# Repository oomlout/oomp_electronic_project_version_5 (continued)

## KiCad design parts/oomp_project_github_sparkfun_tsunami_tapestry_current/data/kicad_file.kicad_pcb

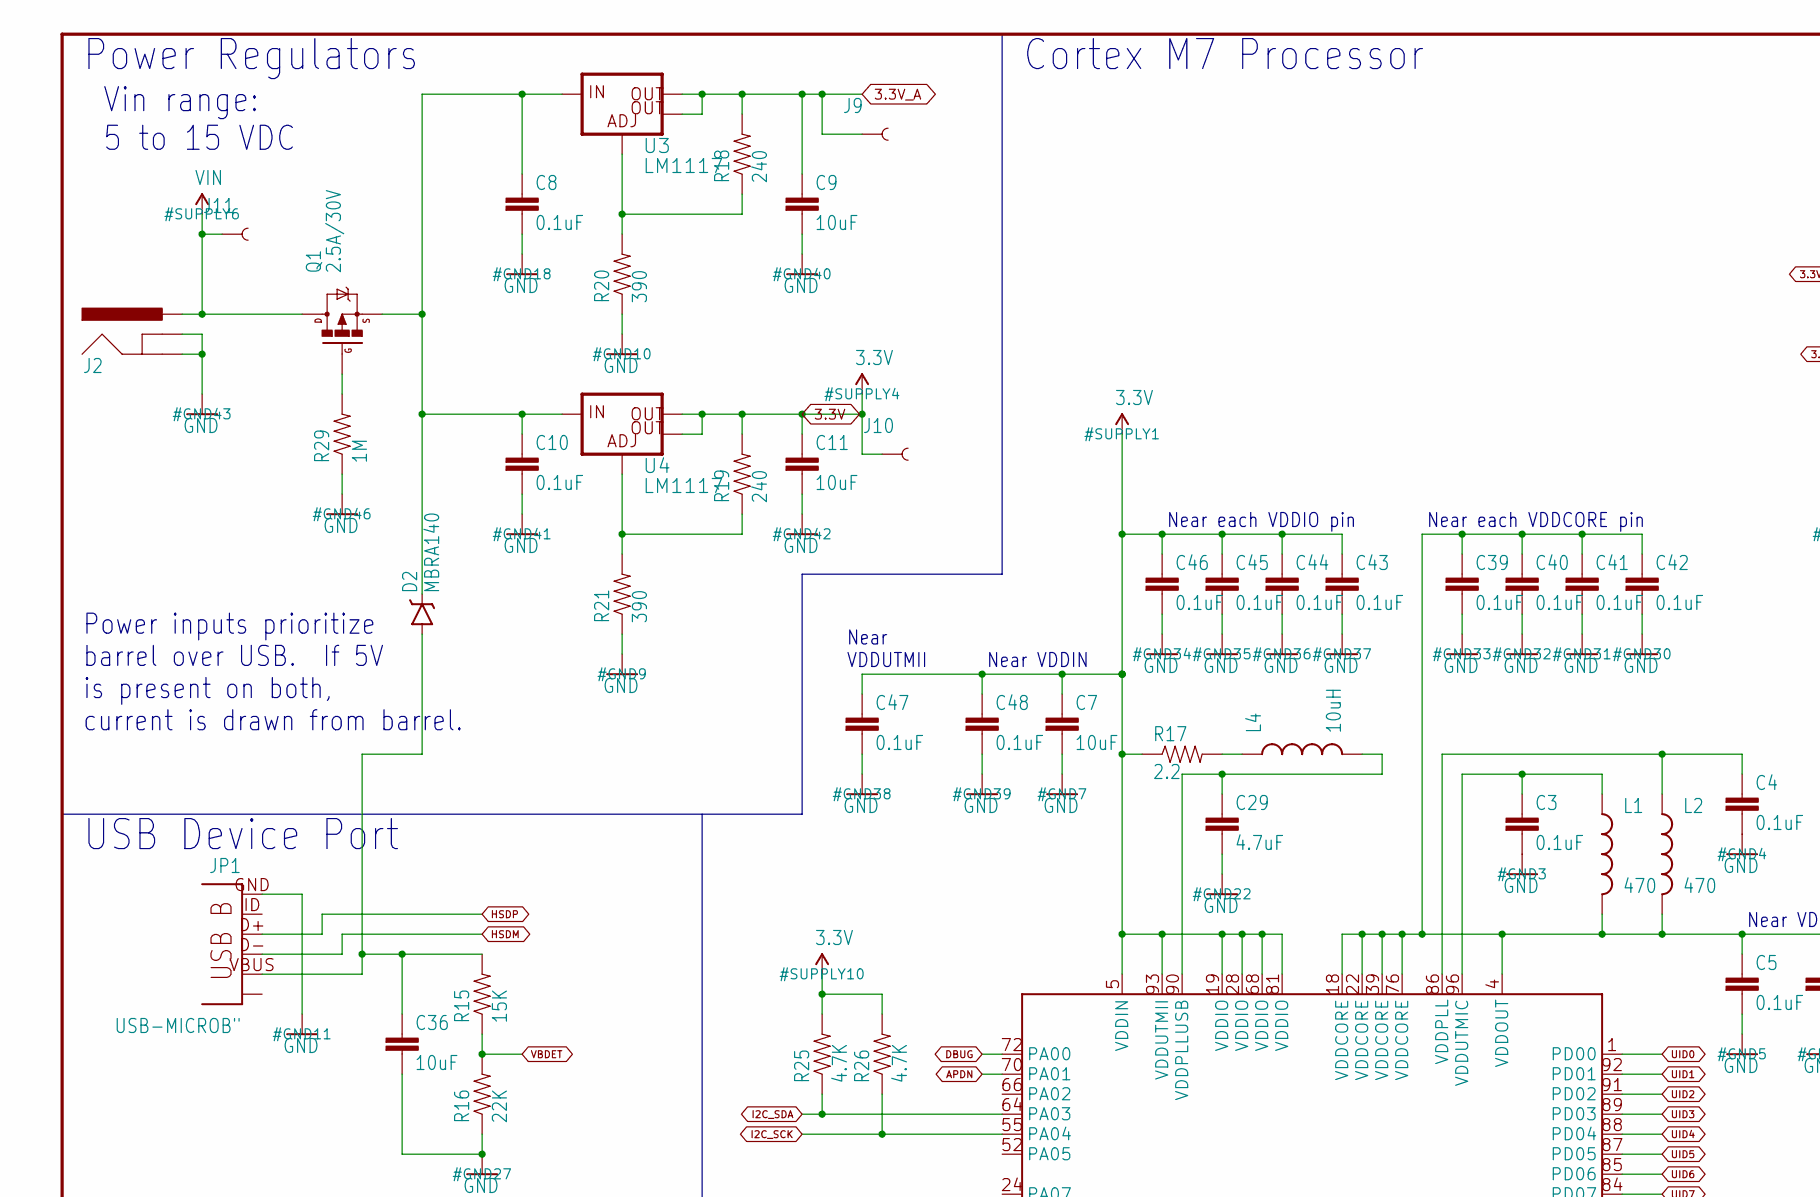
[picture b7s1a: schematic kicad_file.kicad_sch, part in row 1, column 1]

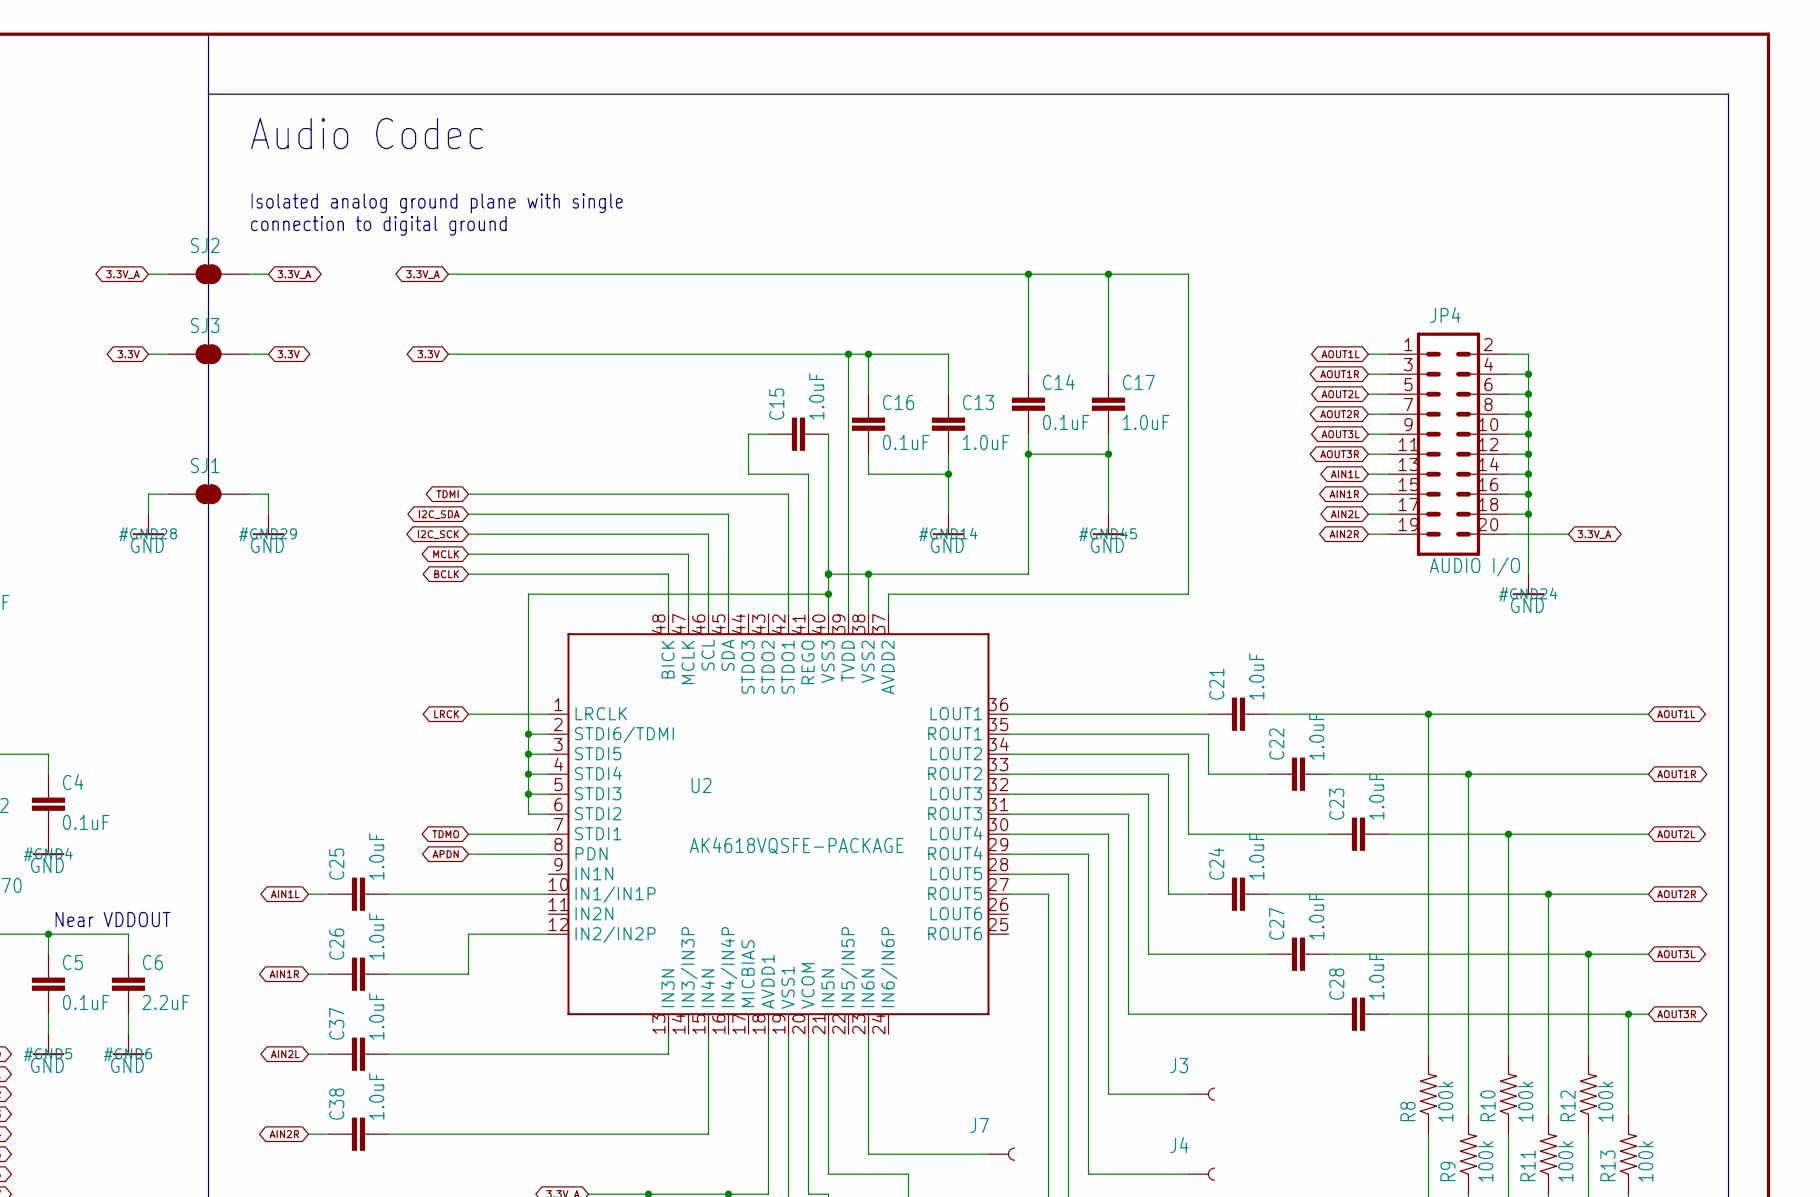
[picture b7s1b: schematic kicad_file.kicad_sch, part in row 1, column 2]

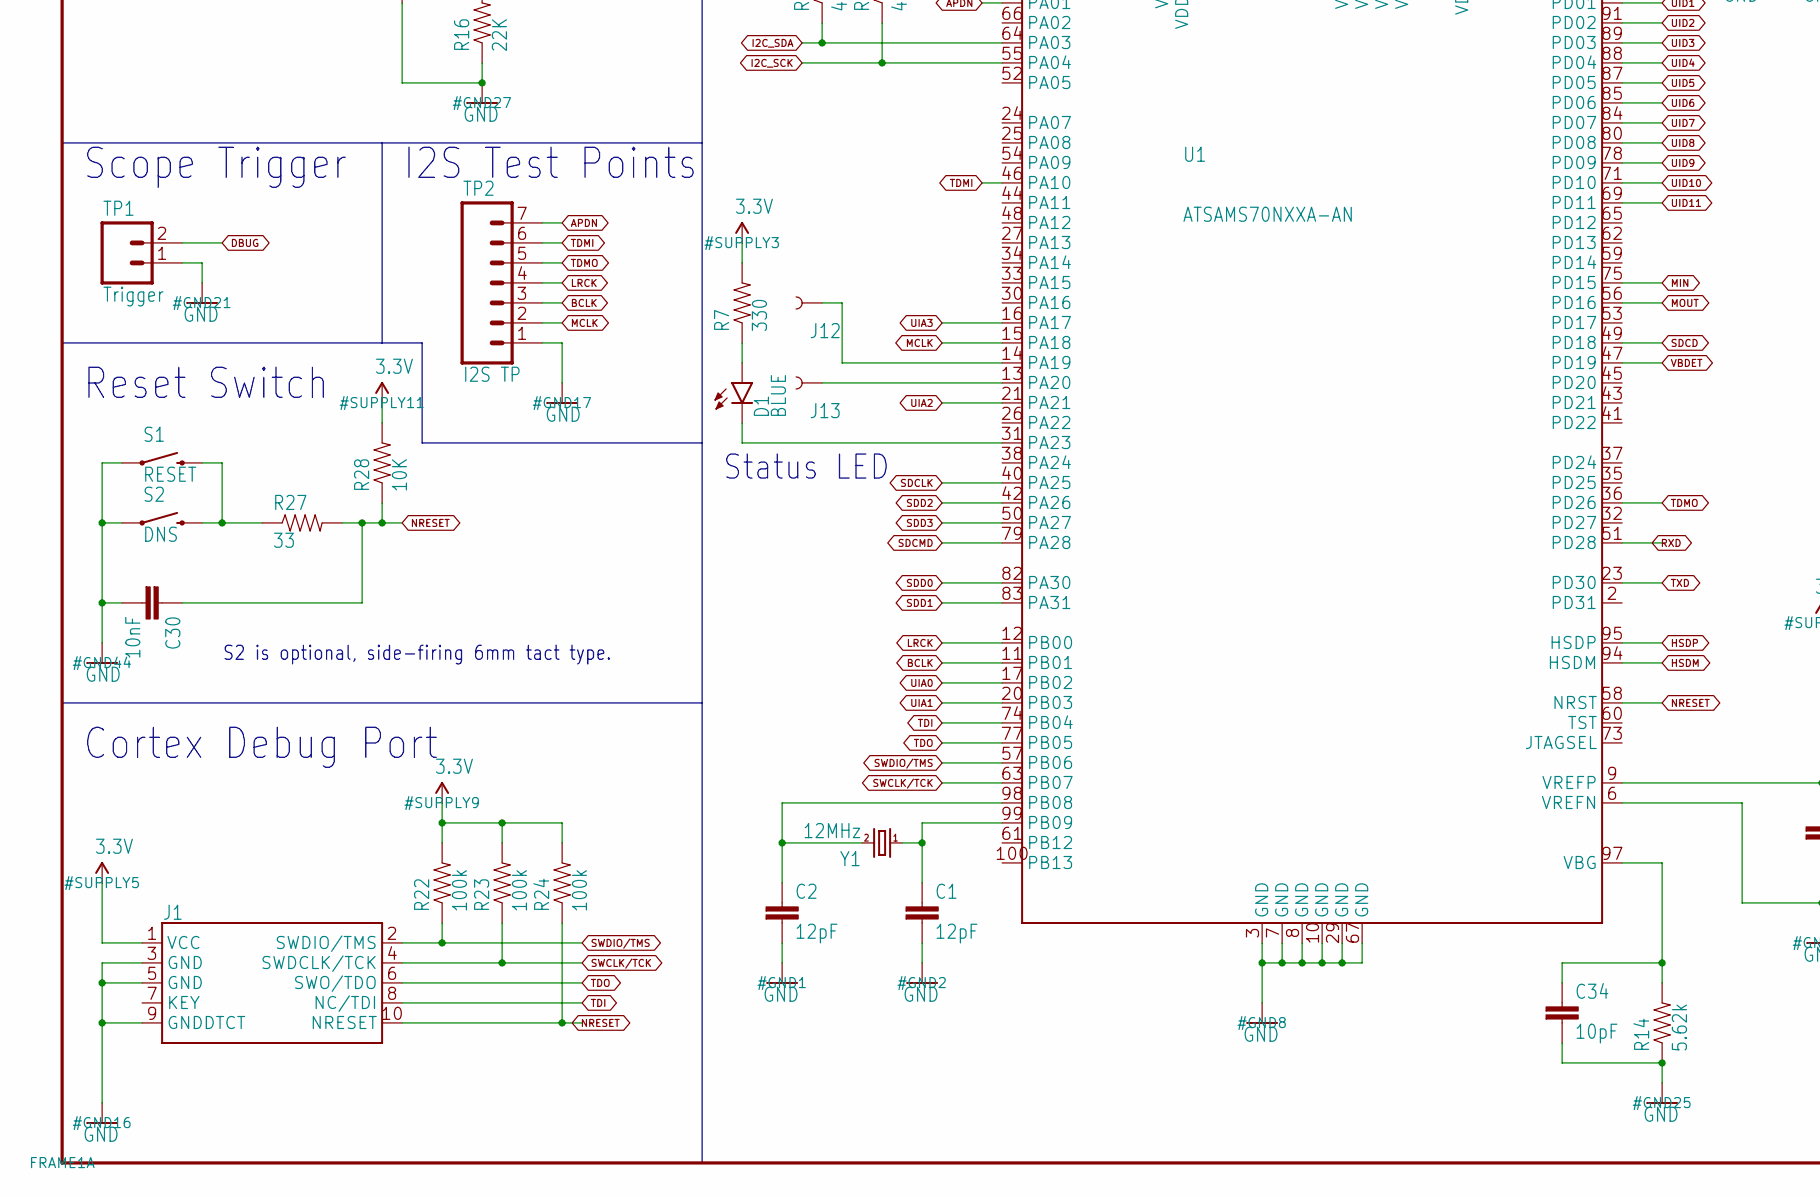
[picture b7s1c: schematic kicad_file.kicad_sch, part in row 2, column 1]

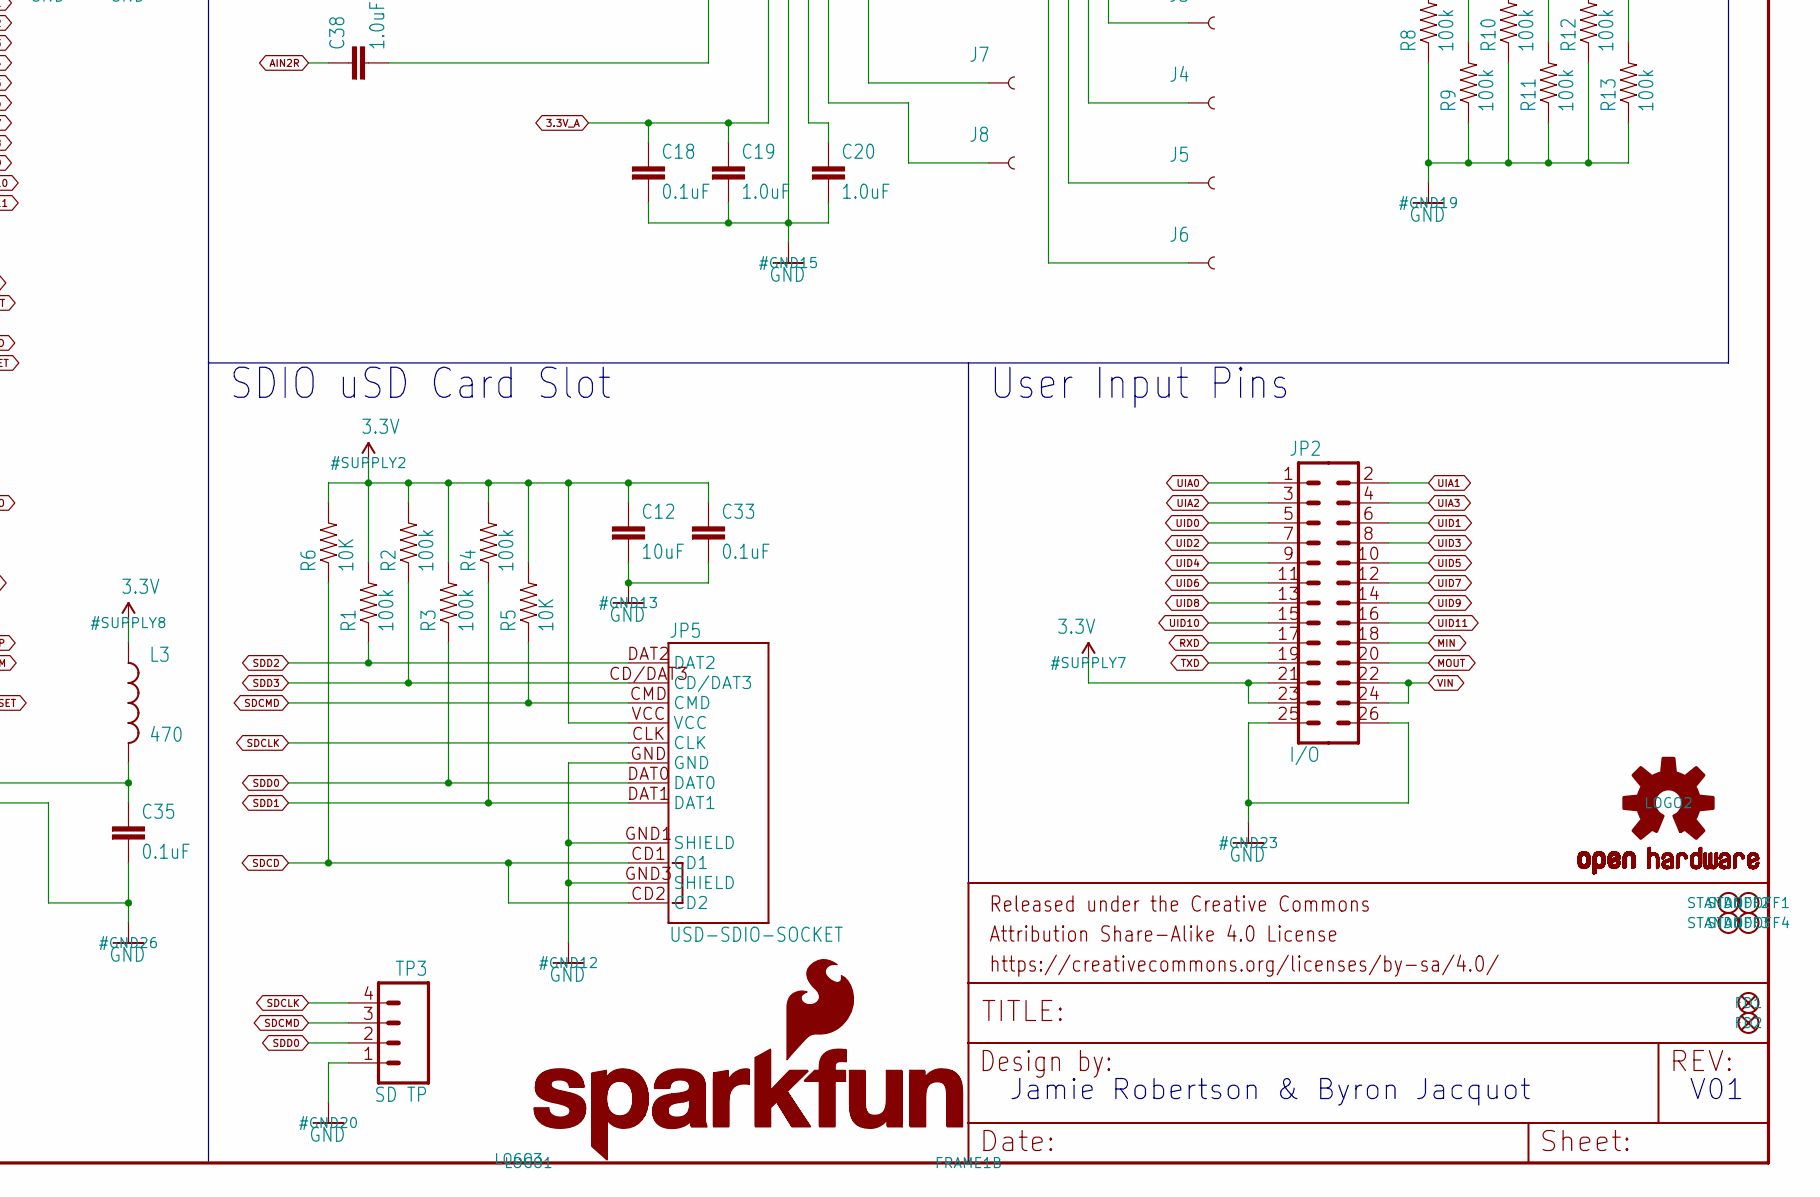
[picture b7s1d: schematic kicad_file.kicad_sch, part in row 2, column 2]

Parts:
C1, C2: 12pF; 0603-CAP
C3, C4, C5, C8, C10, C14, C16, C18, C33, C35, C39, C40, C41, C42, C43, C44, C45, C46, C47, C48: 0.1uF; 0603-CAP
C6: 2.2uF; 0603-CAP
C7, C9, C11, C12, C36: 10uF; 0603-CAP
C13, C15, C17, C19, C20, C21, C22, C23, C24, C25, C26, C27, C28, C37, C38: 1.0uF; 0603-CAP
C29: 4.7uF; 0603-CAP
C30: 10nF; 0603-CAP
C34: 10pF; 0603-CAP
D1: BLUE; LED-0603
D2: MBRA140; SMA-DIODE
FD1, FD2: FIDUCIALUFIDUCIAL; MICRO-FIDUCIAL
FRAME1: FRAME-LEDGER; CREATIVE_COMMONS
J1: CORTEX_DEBUGPTH; 2X5-PTH-1.27MM
J2: POWER_JACK DNS; POWER_JACK_PTH_LOCK
J3: AOUT4L; TP_15TH
J4: AOUT4R; TP_15TH
J5: AOUT5L; TP_15TH
J6: AOUT5R; TP_15TH
J7: AIN3R; TP_15TH
J8: AIN3L; TP_15TH
J9: 3.3VA; TP_15TH
J10: 3.3V; TP_15TH
J11: VIN; TP_15TH
J12: A4; TP_15TH
J13: A5; TP_15TH
JP1: USB-MICROB"; USB-B-MICRO-SMD_V03
JP2: I/O; 2X13
JP4: AUDIO I/O; 2X10
JP5: USD-SDIO-SOCKET; MICRO-SD-SOCKET-SDIO
L1, L2, L3: 470; 0603
L4: 10uH; 0805
LOGO1: SFE_LOGO_NAME_FLAME.2_INCH; SFE_LOGO_NAME_FLAME_.2
LOGO2: OSHW-LOGOM; OSHW-LOGO-M
LOGO3: SFE_LOGO_NAME.2_INCH; SFE_LOGO_NAME_.2
Q1: 2.5A/30V; SOT23-3
R1, R2, R3, R4, R8, R9, R10, R11, R12, R13, R22, R23, R24: 100k; 0603-RES
R5, R6, R28: 10K; 0603-RES
R7: 330; 0603-RES
R14: 5.62k; 0603-RES
R15: 15K; 0603-RES
R16: 22K; 0603-RES
R17: 2.2; 0603-RES
R18, R19: 240; 0603-RES
R20, R21: 390; 0603-RES
R25, R26: 4.7K; 0603-RES
R27: 33; 0603-RES
R29: 1M; 0603-RES
S1: RESET; TACTILE-SWITCH-SMD
S2: DNS; TACTILE-PTH-SIDEEZ
SJ1, SJ2, SJ3: JUMPER-PAD-2-NC_BY_TRACE; PAD-JUMPER-2-NC_BY_TRACE_YES_SILK
STANDOFF1, STANDOFF2, STANDOFF3, STANDOFF4: STAND-OFF
TP1: Trigger; 1X02_NO_SILK
TP2: I2S TP; 1X07_NO_SILK
TP3: SD TP; 1X04_NO_SILK
U1: ATSAMS70NXXA-AN; LQFP100
U2: AK4618VQSFE-PACKAGE; LQFP-48
U3, U4: LM1117; SOT223
Y1: 12MHz; CRYSTAL-SMD-5X3

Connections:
3.3V: C7.1, C11.1, C12.1, C13.1, C16.1, C33.1, C43.1, C44.1, C45.1, C46.1, C47.1, C48.1, J1.1 (VCC), J10.P$1, JP2.21, JP2.23, JP5.VCC, L3.1, R1.2, R2.2, R3.2, R4.2, R5.2, R6.2, R7.2, R17.1, R19.2, R22.2, R23.2, R24.2, R25.2, R26.2, R28.2, SJ3.1, SJ3.2, U1.5 (VDDIN), U1.19 (VDDIO), U1.28 (VDDIO), U1.68 (VDDIO), U1.81 (VDDIO), U1.93 (VDDUTMII), U2.39 (TVDD), U4.2 (OUT), U4.4 (OUT)
3.3V_A: C9.1, C14.1, C17.1, C18.1, C19.1, J9.P$1, JP4.20, R18.2, SJ2.1, SJ2.2, U2.18 (AVDD1), U2.37 (AVDD2), U3.2 (OUT), U3.4 (OUT)
AIN1L: C25.1, JP4.13
AIN1R: C26.1, JP4.15
AIN2L: C37.1, JP4.17
AIN2R: C38.1, JP4.19
AOUT1L: C21.2, JP4.1, R8.2
AOUT1R: C22.2, JP4.3, R9.2
AOUT2L: C23.2, JP4.5, R10.2
AOUT2R: C24.2, JP4.7, R11.2
AOUT3L: C27.2, JP4.9, R12.2
AOUT3R: C28.2, JP4.11, R13.2
APDN: TP2.7, U1.70 (PA01), U2.8 (PDN)
BCLK: TP2.3, U1.11 (PB01), U2.48 (BICK)
DBUG: TP1.2, U1.72 (PA00)
GND: C1.2, C2.2, C3.2, C4.2, C5.2, C6.2, C7.2, C8.2, C9.2, C10.2, C11.2, C12.2, C13.2, C14.2, C15.2, C16.2, C17.2, C18.2, C19.2, C20.2, C29.2, C30.2, C33.2, C34.2, C35.2, C36.2, C39.2, C40.2, C41.2, C42.2, C43.2, C44.2, C45.2, C46.2, C47.2, C48.2, J1.3 (GND), J1.5 (GND), J1.9 (GNDDTCT), J2.GND, J2.GNDBREAK, JP1.GND, JP2.25, JP2.26, JP4.2, JP4.4, JP4.6, JP4.8, JP4.10, JP4.12, JP4.14, JP4.16, JP4.18, JP5.GND, JP5.GND1 (SHIELD), JP5.GND3 (SHIELD), R8.1, R9.1, R10.1, R11.1, R12.1, R13.1, R14.1, R16.1, R20.1, R21.1, R29.1, S1.1, S2.1, SJ1.1, SJ1.2, TP1.1, TP2.1, TP3.1, U1.3 (GND), U1.6 (VREFN), U1.7 (GND), U1.8 (GND), U1.10 (GND), U1.29 (GND), U1.67 (GND), U2.2 (STDI6/TDMI), U2.3 (STDI5), U2.4 (STDI4), U2.5 (STDI3), U2.6 (STDI2), U2.19 (VSS1), U2.38 (VSS2), U2.40 (VSS3)
HSDM: JP1.D-, U1.94 (HSDM)
HSDP: JP1.D+, U1.95 (HSDP)
I2C_SCK: R26.1, U1.55 (PA04), U2.46 (SCL)
I2C_SDA: R25.1, U1.64 (PA03), U2.45 (SDA)
LRCK: TP2.4, U1.12 (PB00), U2.1 (LRCLK)
MCLK: TP2.2, U1.15 (PA18), U2.47 (MCLK)
MIN: JP2.18, U1.75 (PD15)
MOUT: JP2.20, U1.56 (PD16)
unnamed: C2.1, U1.98 (PB08), Y1.3 (2)
unnamed: C1.1, U1.99 (PB09), Y1.1
unnamed: C3.1, L1.1, U1.96 (VDDUTMIC)
unnamed: C29.1, L4.2, U1.90 (VDDPLLUSB)
unnamed: C4.1, L2.1, U1.86 (VDDPLL)
unnamed: C15.1, U2.41 (REGO)
unnamed: C36.1, D2.A, JP1.VBUS, R15.2
unnamed: C8.1, C10.1, D2.C, Q1.2 (S), U3.3 (IN), U4.3 (IN)
unnamed: D1.C, U1.31 (PA23)
unnamed: D1.A, R7.1
unnamed: C20.1, U2.20 (VCOM)
unnamed: C21.1, U2.36 (LOUT1)
unnamed: C26.2, U2.12 (IN2/IN2P)
unnamed: C25.2, U2.10 (IN1/IN1P)
unnamed: C34.1, R14.2, U1.97 (VBG)
unnamed: C35.1, L3.2, U1.9 (VREFP)
unnamed: C22.1, U2.35 (ROUT1)
unnamed: C23.1, U2.34 (LOUT2)
unnamed: C24.1, U2.33 (ROUT2)
unnamed: C27.1, U2.32 (LOUT3)
unnamed: C28.1, U2.31 (ROUT3)
unnamed: C37.2, U2.13 (IN3N)
unnamed: L4.1, R17.2
unnamed: R18.1, R20.2, U3.1 (ADJ)
unnamed: R27.1, S1.3 (2), S2.2
unnamed: C38.2, U2.15 (IN4N)
unnamed: J7.P$1, U2.23 (IN6N)
unnamed: R19.1, R21.2, U4.1 (ADJ)
unnamed: J8.P$1, U2.21 (IN5N)
unnamed: J3.P$1, U2.30 (LOUT4)
unnamed: J4.P$1, U2.29 (ROUT4)
unnamed: J5.P$1, U2.28 (LOUT5)
unnamed: J6.P$1, U2.27 (ROUT5)
unnamed: J12.P$1, U1.14 (PA19)
unnamed: J13.P$1, U1.13 (PA20)
unnamed: Q1.1 (G), R29.2
NRESET: C30.1, J1.10 (NRESET), R24.1, R27.2, R28.1, U1.58 (NRST)
RXD: JP2.17, U1.51 (PD28)
SDCD: JP5.CD1, JP5.CD2, R6.1, U1.49 (PD18)
SDCLK: JP5.CLK, TP3.4, U1.40 (PA25)
SDCMD: JP5.CMD, R5.1, TP3.3, U1.79 (PA28)
SDD0: JP5.DAT0, R3.1, TP3.2, U1.82 (PA30)
SDD1: JP5.DAT1, R4.1, U1.83 (PA31)
SDD2: JP5.DAT2, R1.1, U1.42 (PA26)
SDD3: JP5.CD/DAT3, R2.1, U1.50 (PA27)
SWCLK/TCK: J1.4 (SWDCLK/TCK), R23.1, U1.63 (PB07)
SWDIO/TMS: J1.2 (SWDIO/TMS), R22.1, U1.57 (PB06)
TDI: J1.8 (NC/TDI), U1.74 (PB04)
TDMI: TP2.6, U1.46 (PA10), U2.42 (STDO1)
TDMO: TP2.5, U1.36 (PD26), U2.7 (STDI1)
TDO: J1.6 (SWO/TDO), U1.77 (PB05)
TXD: JP2.19, U1.23 (PD30)
UIA0: JP2.1, U1.17 (PB02)
UIA1: JP2.2, U1.20 (PB03)
UIA2: JP2.3, U1.21 (PA21)
UIA3: JP2.4, U1.16 (PA17)
UID0: JP2.5, U1.1 (PD00)
UID1: JP2.6, U1.92 (PD01)
UID2: JP2.7, U1.91 (PD02)
UID3: JP2.8, U1.89 (PD03)
UID4: JP2.9, U1.88 (PD04)
UID5: JP2.10, U1.87 (PD05)
UID6: JP2.11, U1.85 (PD06)
UID7: JP2.12, U1.84 (PD07)
UID8: JP2.13, U1.80 (PD08)
UID9: JP2.14, U1.78 (PD09)
UID10: JP2.15, U1.71 (PD10)
UID11: JP2.16, U1.69 (PD11)
VBDET: R15.1, R16.2, U1.47 (PD19)
VDDOUT: C5.1, C6.1, C39.1, C40.1, C41.1, C42.1, L1.2, L2.2, U1.4 (VDDOUT), U1.18 (VDDCORE), U1.22 (VDDCORE), U1.39 (VDDCORE), U1.76 (VDDCORE)
VIN: J2.PWR, J11.P$1, JP2.22, JP2.24, Q1.3 (D)

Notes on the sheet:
Audio Codec
Vin range: 5 to 15 VDC
S2 is optional, side-firing 6mm tact type.
V01
USB Device Port
Near VDDIN
Cortex Debug Port
Near each VDDCORE pin
SDIO uSD Card Slot
Status LED
Power Regulators
Scope Trigger
User Input Pins
Jamie Robertson & Byron Jacquot
Power inputs prioritize barrel over USB. If 5V is present on both, current is drawn from barrel.
Reset Switch
Near VDDUTMII
Near VDDOUT
I2S Test Points
Cortex M7 Processor
Near each VDDIO pin
Isolated analog ground plane with single connection to digital ground

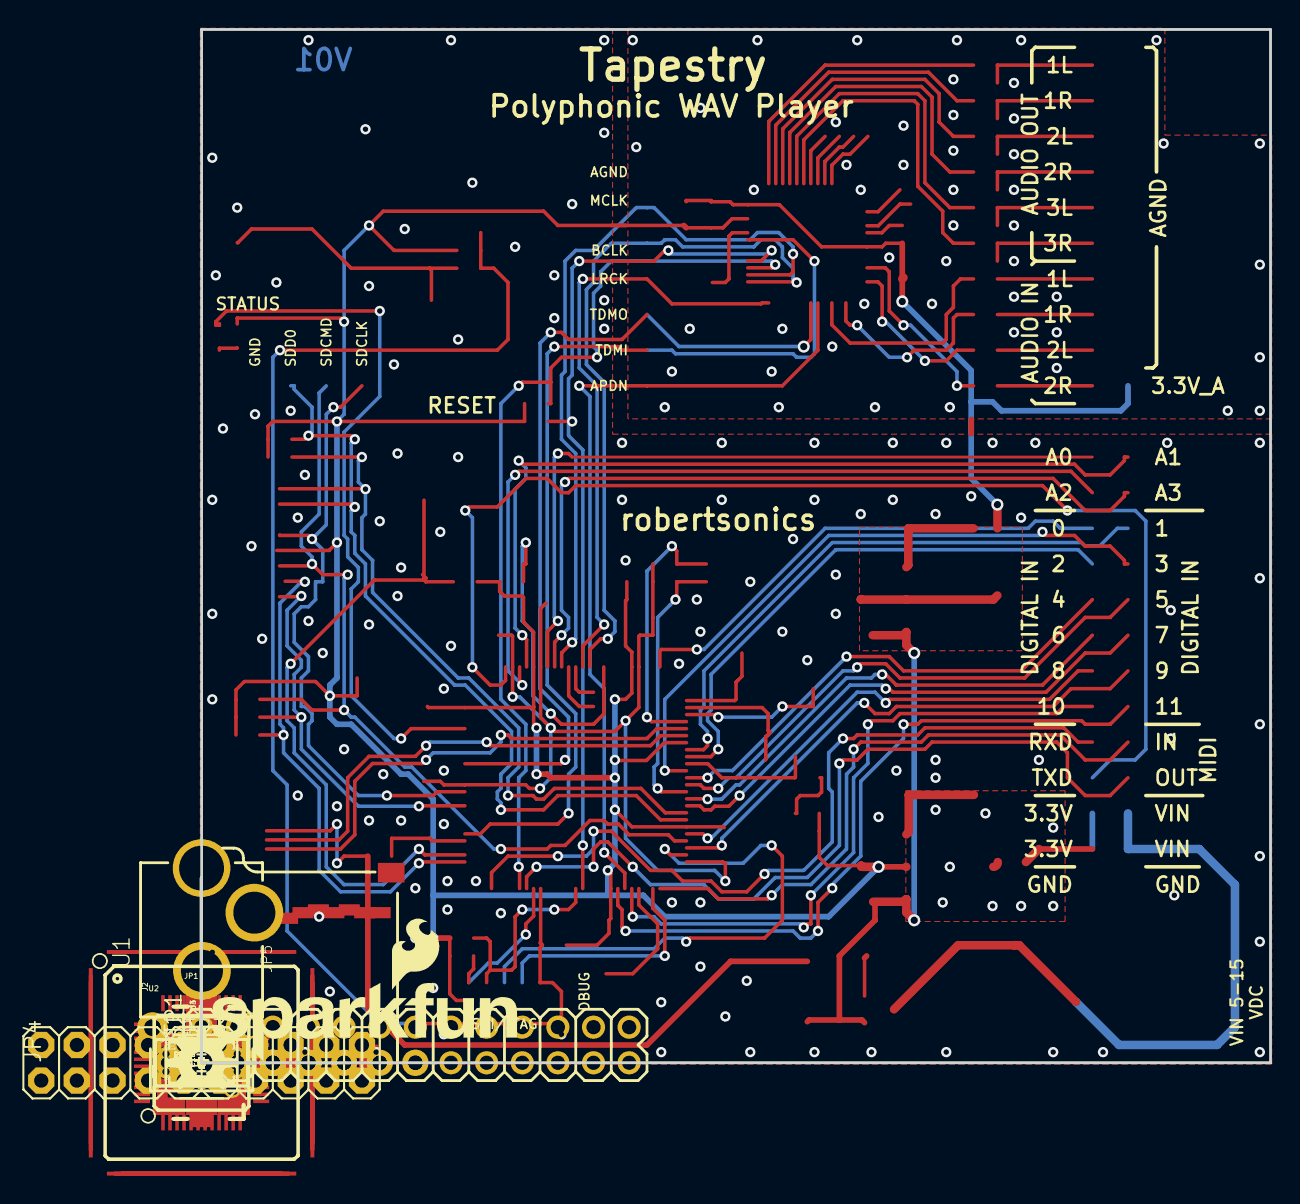
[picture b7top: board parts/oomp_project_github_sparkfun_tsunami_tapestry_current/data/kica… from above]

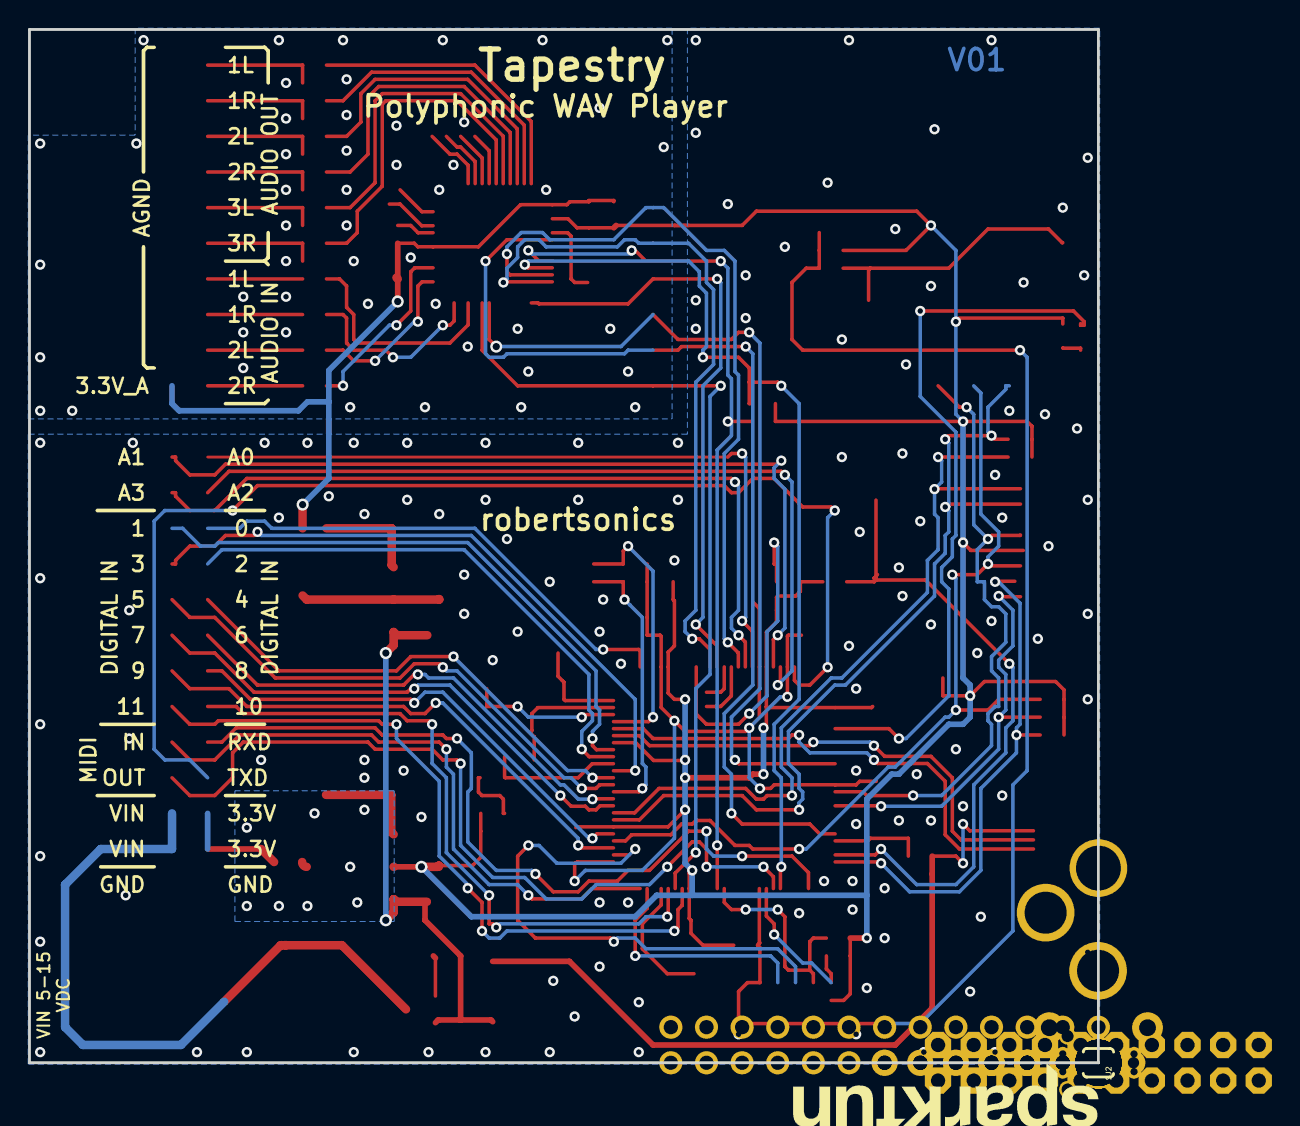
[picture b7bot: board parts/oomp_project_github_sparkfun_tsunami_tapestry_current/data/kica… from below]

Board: 2 copper layers, 76.2 x 73.7 mm, 122 parts (2 on the bottom side), 95 nets.

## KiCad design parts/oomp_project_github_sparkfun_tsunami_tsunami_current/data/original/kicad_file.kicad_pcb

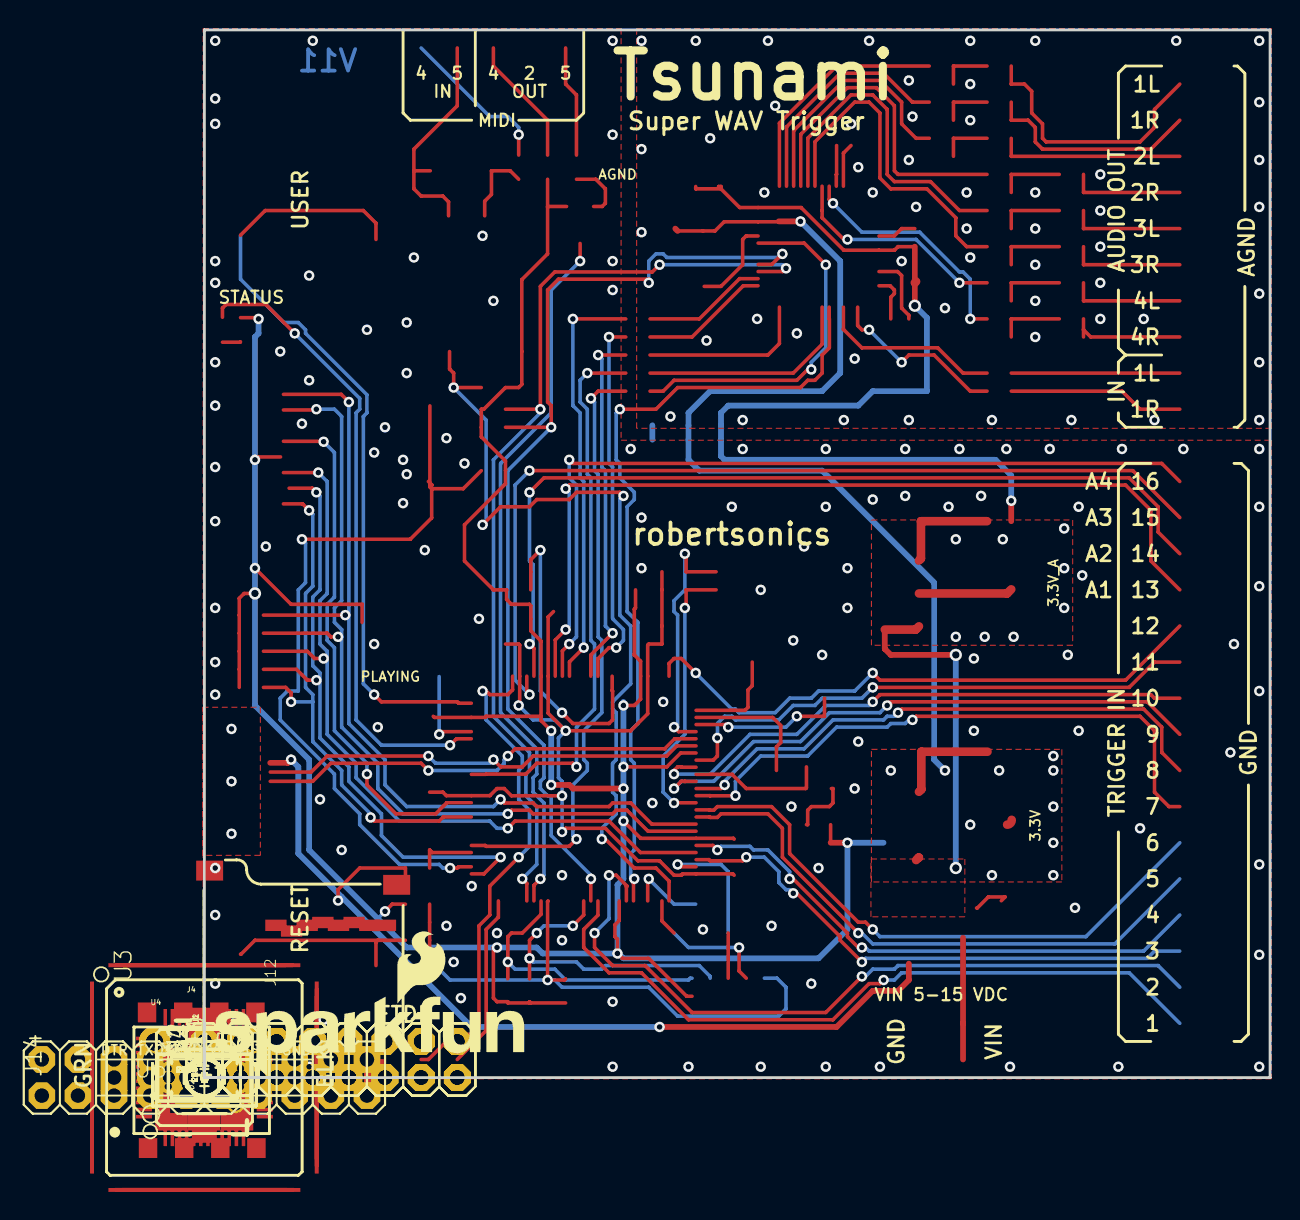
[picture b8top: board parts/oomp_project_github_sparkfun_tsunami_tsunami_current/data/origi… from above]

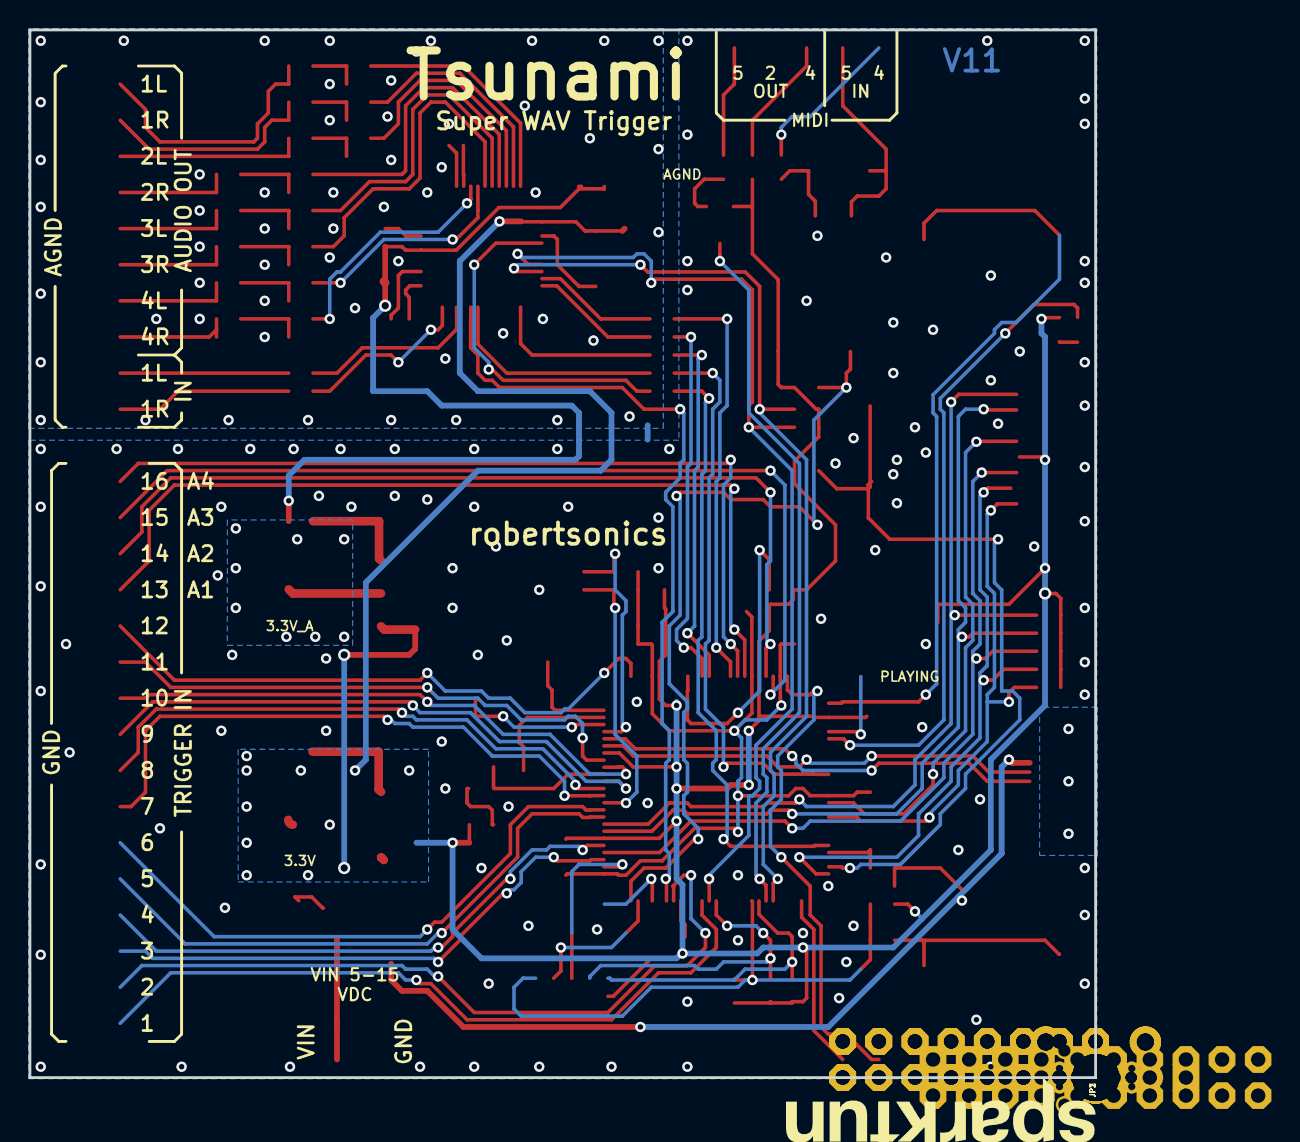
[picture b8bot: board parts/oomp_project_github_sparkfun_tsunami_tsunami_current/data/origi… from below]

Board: 2 copper layers, 74.9 x 73.7 mm, 158 parts (4 on the bottom side), 113 nets.

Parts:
C1: 10nF; 0603-CAP
C2, C5, C6, C11, C27: 10uF; 0603-CAP
C3, C4, C8, C10, C12, C13, C15, C16, C17, C18, C19, C21, C22, C23, C24, C26, C28, C31, C35, C37, C47, C48, C49, C50, C51, C52, C53, C54: 0.1uF; 0603-CAP
C7, C9: 12pF; 0603-CAP
C14: 4.7uF; 0603-CAP
C20: 10pF; 0603-CAP
C25: 2.2uF; 0603-CAP
C29, C30, C32, C33, C34, C36, C38, C39, C40, C41, C42, C43, C44, C45, C46: 1.0uF; 0603-CAP
D1, D3: MBRA140; SMA-DIODE
D2: BLUE; LED-0603
FB1, FB2, FB3: 470; 0603
FD1, FD2: FIDUCIALUFIDUCIAL; MICRO-FIDUCIAL
FRAME1, FRAME2: FRAME-LEDGER; CREATIVE_COMMONS
H1, H2, H3, H4: STAND-OFF
J1: VDC-IN; 1X02
J2: GND-IN; 1X02
J3: DEBUG; 1X01_NO_SILK
J4: USB-MICROB"; USB-B-MICRO-SMD_V03
J5: CORTEX_DEBUGPTH; 2X5-PTH-1.27MM
J6: 3.3VA; 1X01_NO_SILK
J7: 3.3V; 1X01_NO_SILK
J8: PLAYING; 1X01_NO_SILK
J9: FTDI_DEVICE; FTDI_DEVICE_SIDE
J10: TRIG2; 2X8
J11: TRIG1; 2X8
J12: USD-SDIO-SOCKET; MICRO-SD-SOCKET-SDIO
J13: GND; 1X01_NO_SILK
J14: AUDIO I/O; 2X10
J15: MIDI; 1X05_NO_SILK
JP1, JP2, JP3: JUMPER-PAD-2-NC_BY_TRACENO_SILK; PAD-JUMPER-2-NC_BY_TRACE_NO_SILK
L1: 10uH; 0805
LOGO1: SFE_LOGO_NAME.2_INCH; SFE_LOGO_NAME_.2
LOGO4: SFE_LOGO_NAME_FLAME.2_INCH; SFE_LOGO_NAME_FLAME_.2
Q1: 2.5A/30V; SOT23-3
R1: 33; 0603-RES
R2: 1M; 0603-RES
R3, R18, R23: 10K; 0603-RES
R4: 15K; 0603-RES
R5: 22K; 0603-RES
R6, R9, R10, R19, R20, R21, R22, R29, R30, R31, R32, R33, R34, R35, R36: 100k; 0603-RES
R7, R8: 390; 0603-RES
R11, R12: 240; 0603-RES
R13: 330; 0603-RES
R14, R15: 4.7K; 0603-RES
R16: 2.2; 0603-RES
R17: 5.62k; 0603-RES
R24, R25, R26, R27, R28: 100; 0603-RES
R37, R38, R39, R40, R41, R42, R43, R44: 10; 0603-RES
R45, R46, R47, R48: 220; 0603-RES
S1: Reset; TACTILE-SWITCH-SMD
S2, S4: DNS; TACTILE-PTH-SIDEEZ
S3: User; TACTILE-SWITCH-SMD
TP1: AIN2L; TP_15TH
TP2: AIN2R; TP_15TH
TP3: AOUT5L; TP_15TH
TP4: AOUT5R; TP_15TH
TP5: SWDIO/TMS; TP_15TH
TP6: SWCK/TCK; TP_15TH
TP7: TDO; TP_15TH
TP8: TDI; TP_15TH
TP9: NRESET; TP_15TH
U1, U2: LM1117; SOT223
U3: ATSAMS70N20A-AN; LQFP100
U4: AK4618VQ; LQFP-48
U5: 74AHC1G125; SOT23-5
U6: 6N138M; 8-SMD
Y1: 11.2896 MHz; CRYSTAL-OSC-SMD-5X3

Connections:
3.3V: C6.1, C8.1, C10.1, C11.1, C12.1, C13.1, C15.1, C16.1, C27.1, C28.1, C35.1, C36.1, FB3.1, J5.1, J7.1, J12.VCC, JP2.1, JP2.2, R3.2, R6.2, R9.2, R10.2, R12.2, R13.2, R14.2, R15.2, R16.1, R18.2, R19.2, R20.2, R21.2, R22.2, R23.2, R47.2, R48.2, U2.2, U2.4, U3.5, U3.19, U3.28, U3.68, U3.81, U3.93, U4.39, U5.5, U6.8
56: D3.C, R45.2, U6.2
AIN1L: C29.1, J14.17
AIN1R: C30.1, J14.19
AIN2L: TP1.P$1, U4.13
AIN2R: TP2.P$1, U4.15
AOUT1L: C47.1, J14.1, R37.2
AOUT1R: C48.1, J14.3, R38.2
AOUT2L: C49.1, J14.5, R39.2
AOUT2R: C50.1, J14.7, R40.2
AOUT3L: C51.1, J14.9, R41.2
AOUT3R: C52.1, J14.11, R42.2
AOUT4L: C53.1, J14.13, R43.2
AOUT4R: C54.1, J14.15, R44.2
APDN: U3.70, U4.8
BCLK: R26.1, U3.11
BCLK_C: R26.2, U4.48
DBUG: J3.1, U3.72
GND: C1.2, C2.2, C3.2, C4.2, C5.2, C6.2, C7.2, C8.2, C9.2, C10.2, C11.2, C12.2, C13.2, C14.2, C15.2, C16.2, C17.2, C18.2, C19.2, C20.2, C21.2, C22.2, C23.2, C24.2, C25.2, C26.2, C27.2, C28.2, C31.2, C32.2, C33.2, C34.2, C35.2, C36.2, C37.2, C38.2, C47.2, C48.2, C49.2, C50.2, C51.2, C52.2, C53.2, C54.2, J2.1, J2.2, J4.GND, J5.3, J5.5, J5.9, J9.P$6, J10.2, J10.4, J10.6, J10.8, J10.10, J10.12, J10.14, J10.16, J11.2, J11.4, J11.6, J11.8, J11.10, J11.12, J11.14, J11.16, J12.GND, J12.GND1, J12.GND3, J13.1, J14.2, J14.4, J14.6, J14.8, J14.10, J14.12, J14.14, J14.16, J14.18, J14.20, J15.4, JP3.1, JP3.2, R2.1, R5.1, R7.1, R8.1, R17.1, R29.1, R30.1, R31.1, R32.1, R33.1, R34.1, R35.1, R36.1, S1.1, S2.1, S3.1, S4.1, U3.3, U3.6, U3.7, U3.8, U3.10, U3.29, U3.67, U4.2, U4.3, U4.4, U4.5, U4.6, U4.19, U4.38, U4.40, U5.1, U5.3, U6.5, Y1.2, Y1.4
HSDM: J4.D-, U3.94
HSDP: J4.D+, U3.95
I2C_SCK: R15.1, U3.55, U4.46
I2C_SDA: R14.1, U3.64, U4.45
LRCK: R27.1, U3.12
LRCK_C: R27.2, U4.1
MCLK: R25.1, U3.15
MCLK_C: R25.2, U4.47
MIDI-IN-PIN4: J15.1, R45.1
MIDI-IN-PIN5: D3.A, J15.2, U6.3
MIDI-OUT-PIN4: J15.3, R47.1
MIDI-OUT-PIN5: J15.5, R46.2
MIN: R48.1, U3.75, U6.6
MOUT: U3.56, U5.2
unnamed: C7.1, U3.98, Y1.1
unnamed: C9.1, U3.99, Y1.3
unnamed: C19.1, FB1.1, U3.96
unnamed: C14.1, L1.2, U3.90
unnamed: C23.1, FB2.1, U3.86
unnamed: C33.1, U4.41
unnamed: J8.1, U3.30
unnamed: D2.C, U3.31
unnamed: D2.A, R13.1
unnamed: C34.1, U4.20
unnamed: C40.1, U4.36
unnamed: C30.2, U4.12
unnamed: C29.2, U4.10
unnamed: C20.1, R17.2, U3.97
unnamed: C26.1, FB3.2, U3.9
unnamed: C43.1, U4.35
unnamed: C45.1, U4.34
unnamed: C41.1, U4.33
unnamed: C44.1, U4.32
unnamed: C46.1, U4.31
unnamed: C40.2, R31.2, R37.1
unnamed: L1.1, R16.2
unnamed: R7.2, R11.1, U1.1
unnamed: R1.1, S1.3, S2.2
unnamed: C42.2, R30.2, R44.1
unnamed: C39.2, R29.2, R43.1
unnamed: R8.2, R12.1, U2.1
unnamed: C46.2, R36.2, R42.1
unnamed: C39.1, U4.30
unnamed: C42.1, U4.29
unnamed: TP3.P$1, U4.28
unnamed: TP4.P$1, U4.27
unnamed: R46.1, U5.4
unnamed: C44.2, R35.2, R41.1
unnamed: C41.2, R34.2, R40.1
unnamed: C43.2, R32.2, R38.1
unnamed: C45.2, R33.2, R39.1
unnamed: Q1.1, R2.2
NRESET: C1.1, J5.10, R1.2, R3.1, R10.1, TP9.P$1, U3.58
REGINPUTS: C3.1, C4.1, D1.C, Q1.2, U1.3, U2.3
RXD: J9.P$3, U3.51
SDCD: J12.CD1, J12.CD2, R18.1, U3.49
SDCLK: J12.CLK, U3.40
SDCMD: J12.CMD, R23.1, U3.79
SDD0: J12.DAT0, R21.1, U3.82
SDD1: J12.DAT1, R22.1, U3.83
SDD2: J12.DAT2, R19.1, U3.42
SDD3: J12.CD/DAT3, R20.1, U3.50
SHIELD: J4.SHIELD1, J4.SHIELD2, J4.SHIELD3
SWCLK/TCK: J5.4, R9.1, TP6.P$1, U3.63
SWDIO/TMS: J5.2, R6.1, TP5.P$1, U3.57
TDI: J5.8, TP8.P$1, U3.74
TDMI: R24.1, U3.46
TDMI_C: R24.2, U4.42
TDMO: R28.1, U3.36
TDMO_C: R28.2, U4.7
TDO: J5.6, TP7.P$1, U3.77
TXD: J9.P$2, U3.23
UIA1: J10.7, U3.17
UIA2: J10.5, U3.20
UIA3: J10.3, U3.21
UIA4: J10.1, U3.16
UID1: J11.15, U3.65
UID2: J11.13, U3.69
UID3: J11.11, U3.78
UID4: J11.9, U3.80
UID5: J11.7, U3.84
UID6: J11.5, U3.85
UID7: J11.3, U3.87
UID8: J11.1, U3.88
UID9: J10.15, U3.89
UID10: J10.13, U3.91
UID11: J10.11, U3.92
UID12: J10.9, U3.1
USERSW: S3.3, S4.2, U3.26
VBDET: R4.1, R5.2, U3.47
VBUS: C2.1, D1.A, J4.VBUS, R4.2
VCCA: C5.1, C31.1, C32.1, C37.1, C38.1, J6.1, JP1.1, JP1.2, R11.2, U1.2, U1.4, U4.18, U4.37
VDDOUT: C17.1, C18.1, C21.1, C22.1, C24.1, C25.1, FB1.2, FB2.2, U3.4, U3.18, U3.22, U3.39, U3.76
VIN: J1.1, J1.2, Q1.3
